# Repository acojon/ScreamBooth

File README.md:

# ScreamBooth

Here is a potato quality video showing how the Scream Booth works.

A sound activated trigger for my Canon DSLR cameras.  I use this for our annual Halloween Party to setup a photo booth.  The photo booth is sound powered, you have to make a loud sharp sound like a scream, clap, stomp, etc.  The sound then trips the camera and the strobe light letting people take pictures of themselves.  Thus the name "Scream Booth"  It's always been a hit at our halloween party, but in 2017, I ran into a problem.

The scream booth was made possible by a company called Trigger Trap, and a product they sold.  The company sold a dongle, one side connected to your camera's remote trigger, the other connected to the headphone port on your smart phone.  You would download a free app onto your smart phone.  The Trigger Trap app had a number of options for triggering a camera, I used the trigger by sound option to run the Scream Booth.  The idea for the Scream Booth came from one of their blog posts.  It looked like so much fun, I setup one for our Halloween party and it was a hit.

In 2017, the hardware dongle failed, whenever it was plugged into the camera, the shutter on the camera would continuously activate.  This was not a good situation.  Around this time smart phone manufacturers had moved away from installing a headphone jack on their smart phones.  Trigger Trap had gone out of business and you couldn't easily buy a replacement dongle.  Frustrated by these technical failures, I didn't setup a photo booth for that year's halloween party.  This... was a mistake :)  After the party, a couple friends suggested that building a DIY sound trigger was a relatively easy electronics task and encouraged me to try and build a replacement.

I've setup this GitHub repository to share the code, the PCB files, photos, etc. so that if you too would like to setup your own sound powered camera trigger, you can use these resources to help get your own setup.

## Parts List

* 1 x [Adafruit Trinket M0](https://www.adafruit.com/product/3500)
* 1 x [MAX4466 Microphone](https://www.adafruit.com/product/1063)
* 1 x [Simple Shutter Release Cable](https://www.amazon.com/gp/product/B00C0K2PQU/ref=oh_aui_search_detailpage?ie=UTF8&psc=1)
* 1 x [10K Potentiometer](https://www.adafruit.com/product/562)
* 1 x 1000uF Capacitor
* 3 x 100nF Capacitors
* 1 x [Diode](https://www.digikey.com/product-detail/en/on-semiconductor/1N4148TR/1N4148FSCT-ND/9356376)
* 1 x [Signal Relay](https://www.digikey.com/products/en?keywords=ec2-3nu)
* 1 x NPN Transistor. I used this [2N3094](https://www.digikey.com/product-detail/en/on-semiconductor/2N3904BU/2N3904FS-ND/1413)
* 1 x 1K Resistor
* 1 x 10K Resistor
* 1 x Red LED
* 1 x Green LED

Optional Parts:

* Header Pins
* 5v Power Supply for Trinket & Power Cable.  Perhaps a jack to connect/disconnect the power cable
* Fuse
* On/Off Switch
* Connector for Shutter Release cable to Project box (I used a 3.5mm headphone jack and plug)
* Project Box
* Momentary switch to use as reset button

## How does it work

The Scream Booth works by using a microphone to listen to the current sound in the room.  The output is run into a micro controller.  In this case I'm using an Adafruit Trinket M0, but just about any micro controller should work. The micro controller compares the current sound level to a threshold value.  The threshold value is set by the 10k potentiometer. If the current sound level is higher than the threshold level, the micro controller sets the LED and Camera PINS to HIGH for 500 milliseconds (1/2 a second.) This turns on the transistor, which turns on the relay.  The relay connects the camera's ground and "Full Press" pins together which triggers the shutter on the camera.

### Things I learned picking a microphone breakout board

The most important thing I learned while testing microphone breakout boards was to test the microphone and see if there is a "loud noise" cutout.  If the microphone mutes the output (or does some clever filtering to keep the loud noise from appearing in the output) then this microphone isn't going to work for the Scream Booth.

### Things I learned about camera remote trigger jacks

The camera I use for the Scream Booth is a Canon DSLR.

The manufactured remote controls work by connecting the Half Press, or Full Press pins to the camera's ground pin.  I ordered an inexpensive remote trigger from Amazon and took it apart to confirm I understood the pinout and the behavior of the remote trigger cable.  Different camera manufacturers have different types of connectors to their remote trigger, but many followed the same approach: Connect pin to camera ground to trigger the camera shutter.

### Things I learned about using a relay

In this project, I used a relay to trigger the camera.  You could use a opto-isolator to replace the relay.  If you know more than I do about electronics (not hard, I'm only a hobbyist) then there may be other options to momentarily connect the two pins on the camera.  I'm not here to judge :)  The relay's coil is connected to 3.3v, and to an NPN transistor configured as a low side switch.  There's a pull down resistor on the transistor's gate pin.  The Trinket can trigger the transistor.  There's a flyback diode in parallel with the relay coil to keep the transistor safe.

### Things I learned about using an Adafruit Trinket M0

I used this micro controller because it's inexpensive, and because I have a couple on hand :) You can use a different micro controller, or you can skip the micro controller if you know how to build this sort of trigger without one.

## PCB

This was the first PCB I designed.  It actually took three tries to get a board that worked.  If you are using the same parts that I'm using, please feel free to use the Scream Booth Gerber Files.zip to order some PCBs of your own. :)

## Final Disclaimer

I'm not an electronics expert, I have a hobby level of understanding about electronics.  If you see a mistake, please let me know.  If you know how to modify something, or alter the parts, etc., please do.

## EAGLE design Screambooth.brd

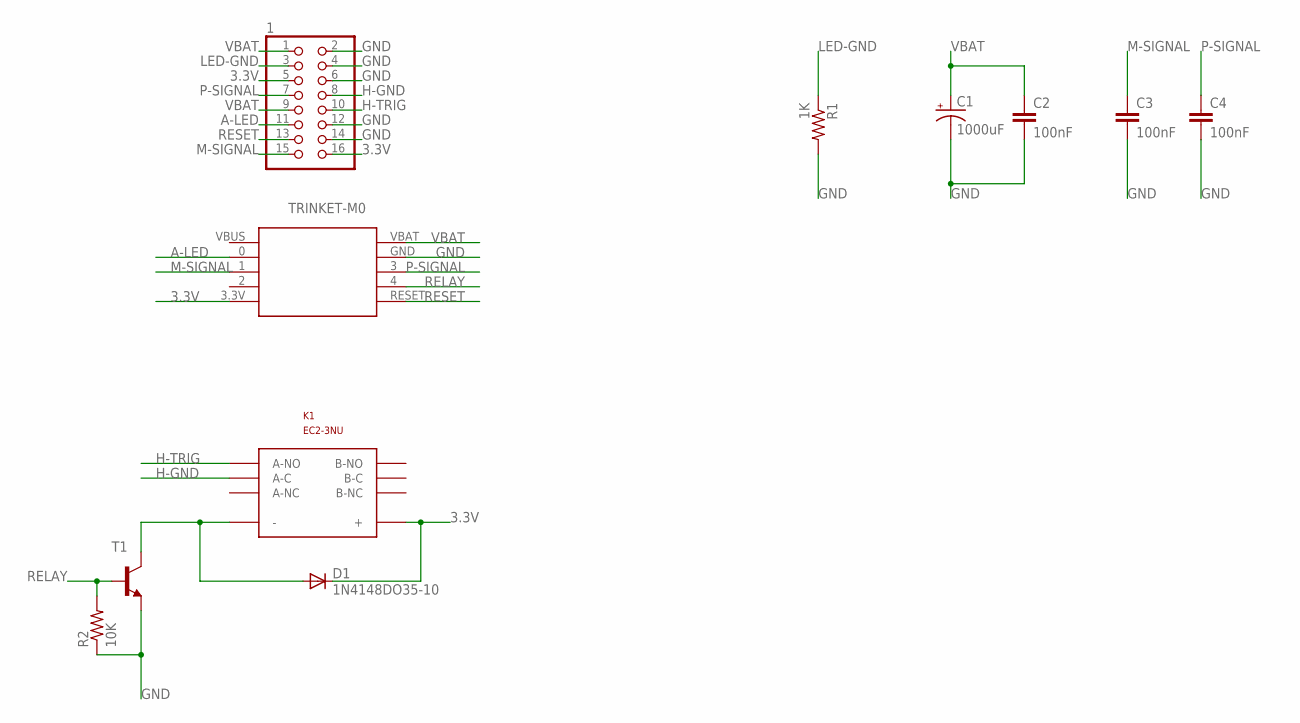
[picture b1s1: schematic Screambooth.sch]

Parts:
1: PINHD-2X8; 2X08
C1: 1000uF; E5-10,5
C2, C3, C4: 100nF; C050-030X075
D1: 1N4148DO35-10; DO35-10
K1: EC2-3NU; EC2-RELAY
R1: 1K; 0207/10
R2: 10K; 0207/10
T1: 2N3904; TO92
TRINKET-M0: TRINKET-M0

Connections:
3.3V: 1.5, 1.16, D1.C, K1.+, TRINKET-M0.3.3V
A-LED: 1.11, TRINKET-M0.0
GND: 1.2, 1.4, 1.6, 1.12, 1.14, C1.-, C2.2, C3.2, C4.2, R1.2, R2.1, T1.3 (E), TRINKET-M0.GND
H-GND: 1.8, K1.A-C
H-TRIG: 1.10, K1.A-NO
LED-GND: 1.3, R1.1
M-SIGNAL: 1.15, C3.1, TRINKET-M0.1
unnamed: D1.A, K1.-, T1.1 (C)
P-SIGNAL: 1.7, C4.1, TRINKET-M0.3
RELAY: R2.2, T1.2 (B), TRINKET-M0.4
RESET: 1.13, TRINKET-M0.RESET
VBAT: 1.1, 1.9, C1.+, C2.1, TRINKET-M0.VBAT

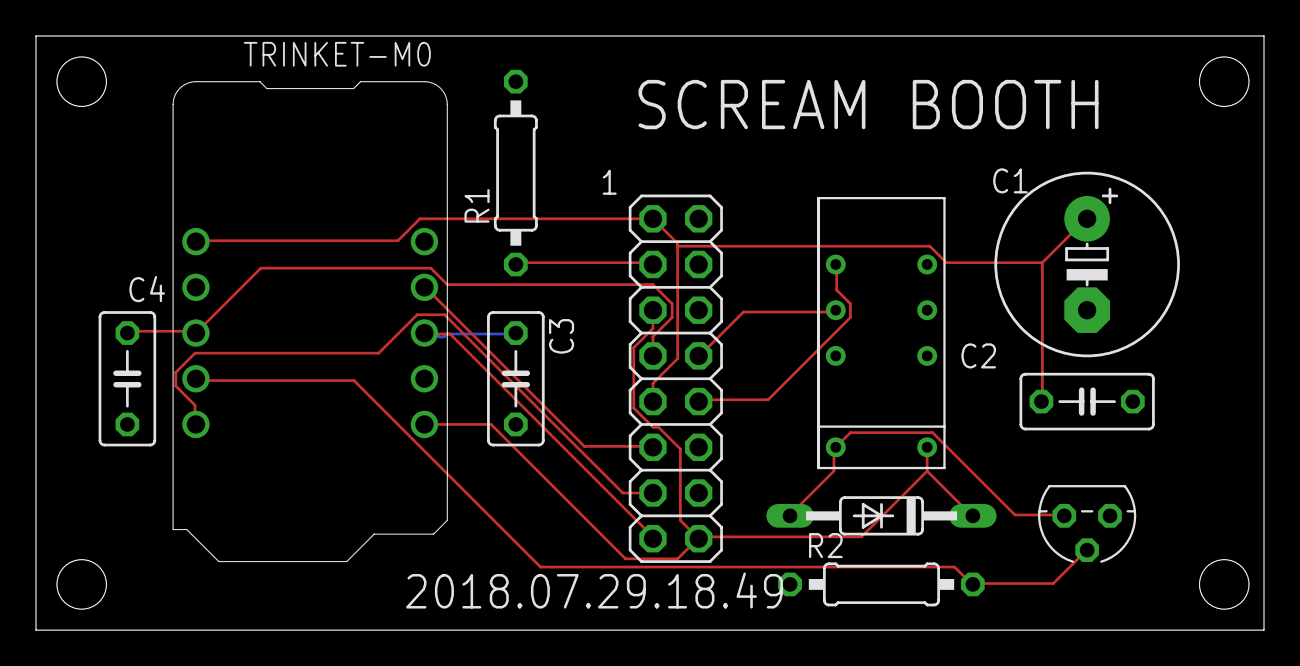
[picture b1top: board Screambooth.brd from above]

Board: 2 copper layers, 68.2 x 33.0 mm, 11 parts (0 on the bottom side), 12 nets.

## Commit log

2018-09-30 Add Spell Checked Words
2018-09-30 Add Arduino Sketch
2018-09-30 Add the Process Photos
2018-09-30 Add Eagle Schematic and Board
2018-09-30 Add Files for Ordering PCB
    These are the files I uploaded to JLBPCB.com to order the PCBs.
2018-09-30 Add Camera Pinout diagram
2018-09-30 Adding detail to Readme
2018-09-30 Fixing Youtube link
2018-09-30 Add a parts LIst
2018-09-30 Fine Tuning of the Readme language
2020-02-08 Rebuilding in Circuit Python
2020-02-08 Make the led blink
    When it's in the db filter timeframe
2020-02-08 Add some commenting
2020-02-08 Change deadband filter behavior
2023-10-27 Add deadband filter
2023-10-27 Hold the shutter for a shorter period of time
